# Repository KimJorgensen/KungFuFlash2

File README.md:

# Kung Fu Flash 2

The version in the repo is optimized for mass production, is 100% SMT

Cartridge for the Commodore 64 that packs a punch.

Kung Fu Flash 2 is the big brother of [Kung Fu Flash](https://github.com/KimJorgensen/KungFuFlash). It has a faster microcontroller with more memory and I/O pins, allowing for additional functionality.

**Currently, this project is considered experimental** and provides the same features as Kung Fu Flash, with these notable exceptions:

* CRT files are loaded into RAM, not flash, making large CRT files startup faster. However, changes to EasyFlash cartridges are lost if power is turned off, unless saved via the menu first
* The cartridge detects if the C64/C128 is reset. This allows the use of an additional reset button on the C64 or the built-in reset button on the C128
* REU emulation has been added

Kung Fu Flash 2 can emulate different cartridge types, load PRG files and use D64 disk images.
Just place your desired CRT, PRG or D64 files on a FAT formatted microSD card and use the built-in launcher to execute them.

## Hardware

There are three buttons on the cartridge; a reset button, a menu button for starting the launcher, and a special button that is used by the freezer cartridges.

The form factor is similar to Kung Fu Flash and it should be possible to use the same cartridge cases.
It could be the Stumpy Cartridge Case from TFW8b or the 3D printed cartridge case designed by bigby, [see here](https://www.thingiverse.com/thing:4153414).

The gerber files and BOM can be found [here](https://github.com/KimJorgensen/KungFuFlash2/releases/tag/v2.00).

## Supported Cartridges

The following cartridge types are currently supported:

* Generic cartridge (8k, 16k, Ultimax)
* Action Replay v4.x/v5/v6
* KCS Power Cartridge
* Final Cartridge III(+)
* Simons' BASIC
* Fun Play, Power Play
* Super Games
* Ocean type 1
* Epyx Fastload
* C64 Game System, System 3
* WarpSpeed
* Dinamic
* Zaxxon, Super Zaxxon
* Magic Desk, Domark, HES Australia
* Super Snapshot v5
* Comal-80
* Ross
* EasyFlash
* Prophet64
* Freeze Frame
* Freeze Machine
* MACH 5
* Pagefox
* RGCD, Hucky
* Drean
* C128 Generic cartridge (external function ROM)
* WarpSpeed 128

## Supported File Types

The following file types are currently supported:

* Cartridge (CRT)
* C64/C128 generic cartridge (ROM, BIN)
* Disk image (D64, D71, D81)
* Tape image (T64)
* Program (PRG, P00)
* Firmware update (UPD)
* Text document (TXT, NFO, 1ST)

## REU Emulation

Kung Fu Flash 2 can emulate a 1 Mb REU (RAM Expansion Unit) simultaneously with disk drive emulation.
The REU is enabled in the settings menu (F5) and active when:

* A program is executed using the default option (RETURN)
* A disk image or directory is mounted using "Mount" in the file options menu (SHIFT+RETURN)
* BASIC is started via F6 (C128) or F7 (C64) in the launcher

The REU will not be active when emulating cartridges (CRT files)

## USB Port

The USB port allows programs or disk images to be transferred from/to a PC using the EasyFlash 3 USB protocol.
The USB port is active when:

* The Kung Fu Flash 2 launcher is running
* A program is started using "Load" in the file options menu (SHIFT+RETURN)
* BASIC is started via F7 in the launcher **and** REU emulation is disabled in the settings menu (F5)

Kung Fu Flash 2 shows up as a standard serial port when connected to a PC not requiring any custom drivers to be installed.
This means, however, that the EasyFlash 3 program on the PC side must be modified to support Kung Fu Flash.

The repository of the original Kung Fu Flash contains a modified version of [EasyFlash 3 USB Utilities](https://github.com/KimJorgensen/KungFuFlash/tree/master/3rd_party/ef3utils)
and [EasyFlash 3 BBS](https://github.com/KimJorgensen/KungFuFlash/tree/master/3rd_party/ef3bbs) which will also work with the Kung Fu Flash 2.

## Firmware Update

Just place the KungFuFlash_v2.xx.upd file on the SD card and select the file in the launcher to initiate the firmware update.
The newest firmware can be found [here](https://github.com/KimJorgensen/KungFuFlash2/releases/).

For initial firmware installation, [see here](firmware/README.md).

## Limitations

Kung Fu Flash 2 is a so called Software Defined Cartridge where a fast microcontroller emulates cartridge hardware in software.
This makes it extremely flexible, allowing different cartridge types to be supported at a relative low cost.

However, it can be challenging to get the C64 bus timing correct in software and in some places the timing is very close to the limit.
Even though Kung Fu Flash 2 has been tested on different models of the Commodore 64, there is a chance that it doesn't work correctly on your specific model, or requires [phi2 offset adjustment](firmware/README.md#diagnostic).
Use it at your own risk!

Kung Fu Flash 2 will work with the PAL and NTSC version of the Commodore 64 or Commodore 128.

Disk drive emulation is using kernal vectors and will not work with fast loaders or software that uses direct hardware access which a lot of games does.
Currently REL files are not supported and only a subset of the Commodore DOS commands are supported.

## Thanks

Kung Fu Flash 2 was based on or uses other open source projects:

* [Kung Fu Flash](https://github.com/KimJorgensen/KungFuFlash)
* [EasyFlash 3](https://bitbucket.org/skoe/easyflash) by Thomas Giesel
* [Draco Browser](https://csdb.dk/release/?id=89910) by Sascha Bader
* [fatfs-stm32](https://github.com/colosimo/fatfs-stm32) by Aurelio Colosimo
* [FatFs](http://elm-chan.org/fsw/ff/00index_e.html) by ChaN
* [libusb_stm32](https://github.com/dmitrystu/libusb_stm32) by Dmitry Filimonchuk
* [OpenC64Cart](https://github.com/SukkoPera/OpenC64Cart) by Giorgioggì
* [Disk2easyflash](https://csdb.dk/release/?id=150323) by ALeX Kazik

and a few others. Please check the individual files for their license.

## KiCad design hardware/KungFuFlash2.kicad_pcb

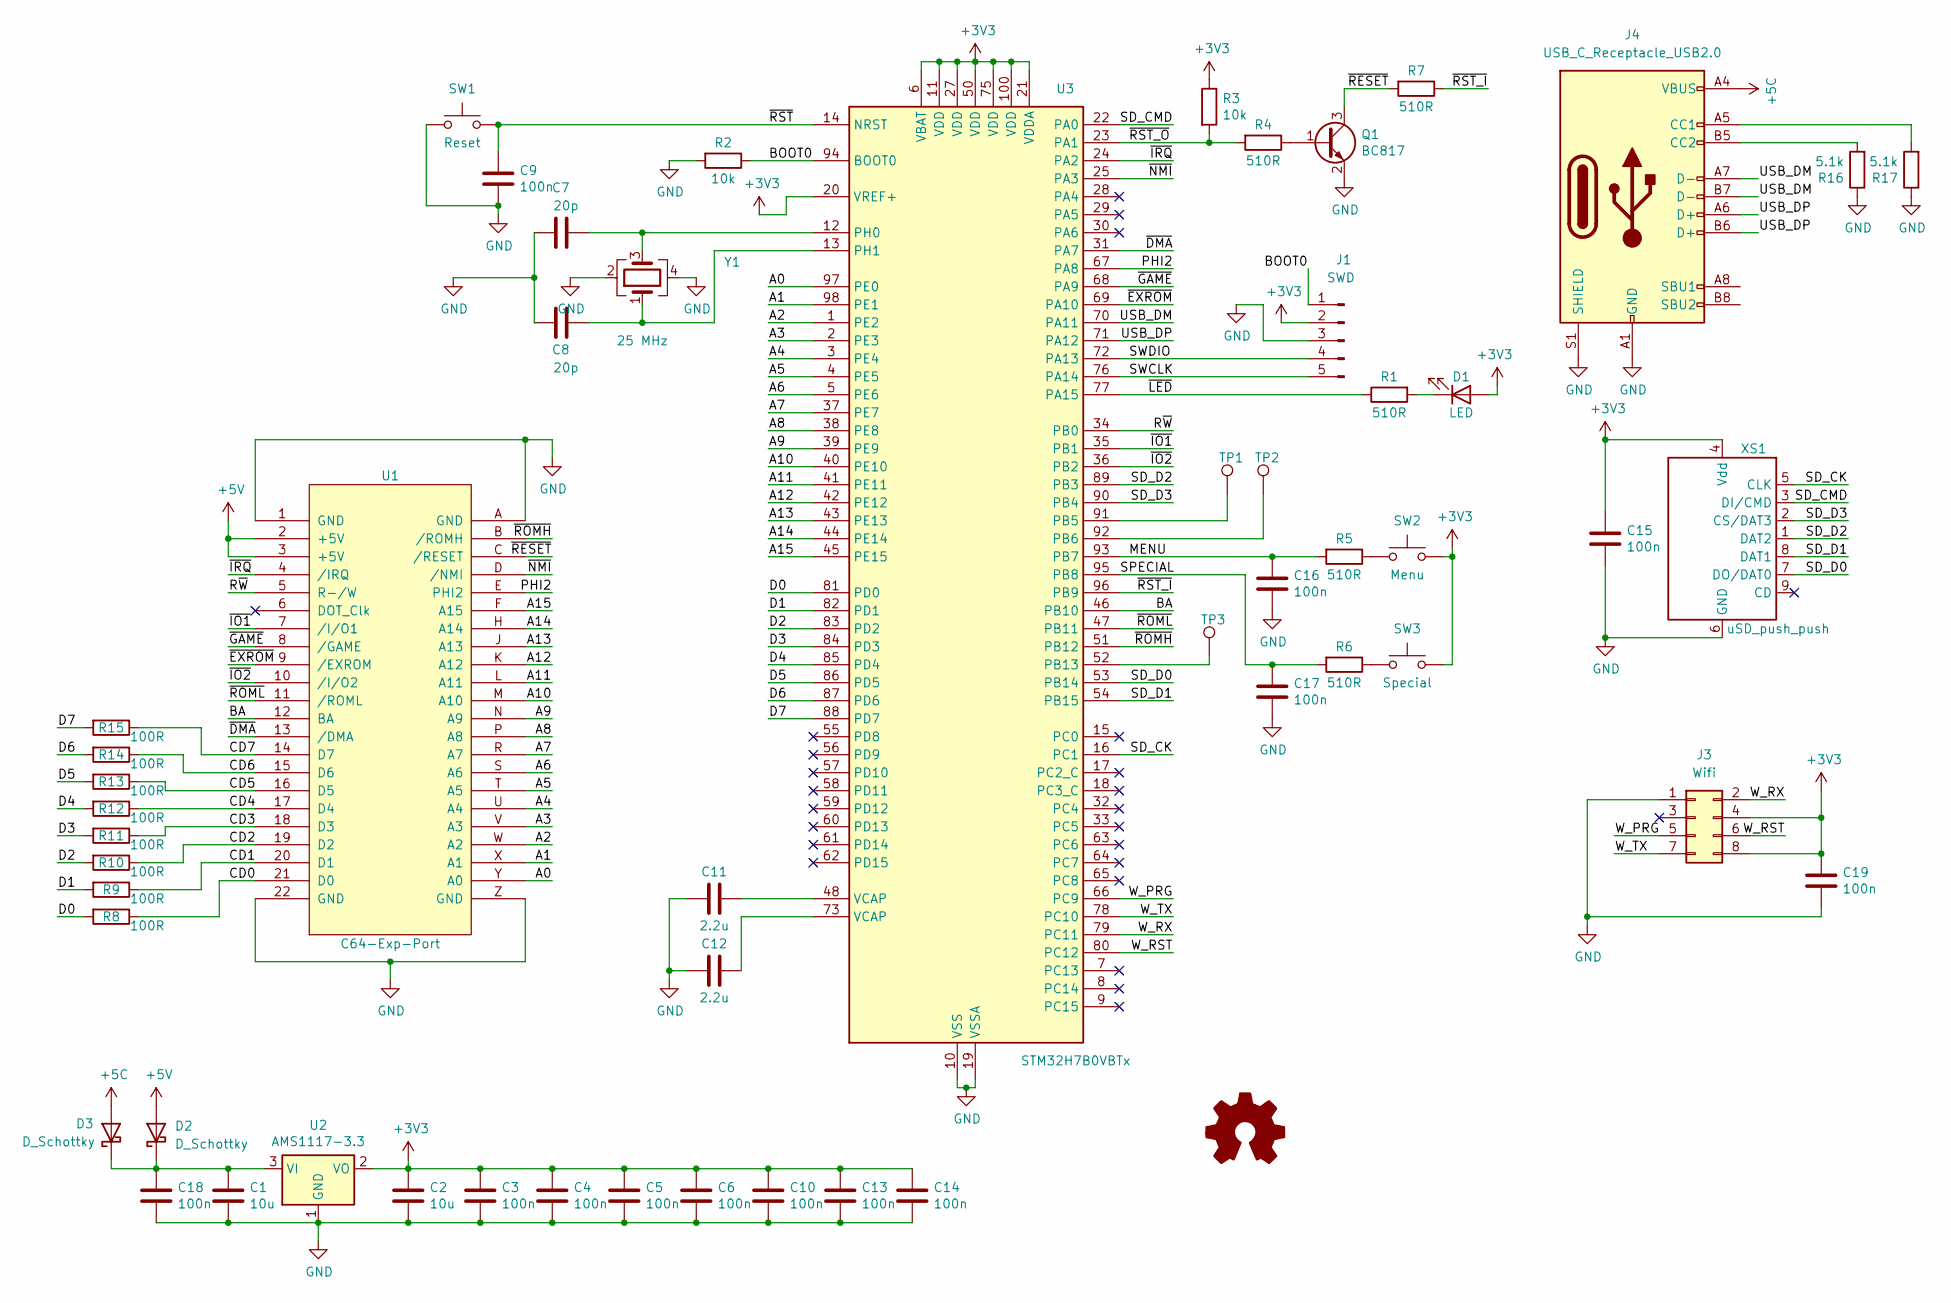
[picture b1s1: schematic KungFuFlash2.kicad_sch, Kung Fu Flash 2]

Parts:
C1, C2: 10u; C_0805_2012Metric_Pad1.18x1.45mm_HandSolder
C3, C4, C5, C6, C9, C10, C13, C14, C15, C16, C17, C18, C19: 100n; C_0603_1608Metric_Pad1.08x0.95mm_HandSolder
C7, C8: 20p; C_0603_1608Metric_Pad1.08x0.95mm_HandSolder
C11, C12: 2.2u; C_0805_2012Metric_Pad1.18x1.45mm_HandSolder
D1: LED; LED_0805_2012Metric_Pad1.15x1.40mm_HandSolder
D2, D3: D_Schottky; D_SMA_Handsoldering
J1: SWD; PinHeader_1x05_P2.54mm_Vertical
J3: Wifi; PinSocket_2x04_P2.54mm_Vertical
J4: USB_C_Receptacle_USB2.0; USB_C_Receptacle_XKB_U262-16XN-4BVC11
Q1: BC817; SOT-23
R1, R4, R5, R6, R7: 510R; R_0805_2012Metric_Pad1.20x1.40mm_HandSolder
R2, R3: 10k; R_0805_2012Metric_Pad1.20x1.40mm_HandSolder
R8, R9, R10, R11, R12, R13, R14, R15: 100R; R_0805_2012Metric_Pad1.20x1.40mm_HandSolder
R16, R17: 5.1k; R_0805_2012Metric_Pad1.20x1.40mm_HandSolder
SW1: Reset; SW_SPST_PTS645
SW2: Menu; SW_SPST_PTS645
SW3: Special; SW_SPST_PTS645
TP1, TP2, TP3: TestPoint_Pad_1.0x1.0mm
U1: C64-Exp-Port; C64-Cart
U2: AMS1117-3.3; SOT-223-3_TabPin2
U3: STM32H7B0VBTx; LQFP-100_14x14mm_P0.5mm
XS1: uSD_push_push; Conn_uSDcard
Y1: 25 MHz; Crystal_SMD_3225-4Pin_3.2x2.5mm

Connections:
+3V3: C2.1, C3.1, C4.1, C5.1, C6.1, C10.1, C13.1, C14.1, C15.1, C19.1, D1.2 (A), J1.2, J3.4, J3.8, R3.1, SW2.1, SW3.1, U2.2 (VO), U3.6 (VBAT), U3.11 (VDD), U3.20 (VREF+), U3.21 (VDDA), U3.27 (VDD), U3.50 (VDD), U3.75 (VDD), U3.100 (VDD), XS1.4 (Vdd)
+5C: D3.2 (A), J4.A4 (VBUS), J4.A9 (VBUS), J4.B4 (VBUS), J4.B9 (VBUS)
+5V: D2.2 (A), U1.2 (+5V), U1.3 (+5V)
/A0: U1.Y (A0), U3.97 (PE0)
/A1: U1.X (A1), U3.98 (PE1)
/A2: U1.W (A2), U3.1 (PE2)
/A3: U1.V (A3), U3.2 (PE3)
/A4: U1.U (A4), U3.3 (PE4)
/A5: U1.T (A5), U3.4 (PE5)
/A6: U1.S (A6), U3.5 (PE6)
/A7: U1.R (A7), U3.37 (PE7)
/A8: U1.P (A8), U3.38 (PE8)
/A9: U1.N (A9), U3.39 (PE9)
/A10: U1.M (A10), U3.40 (PE10)
/A11: U1.L (A11), U3.41 (PE11)
/A12: U1.K (A12), U3.42 (PE12)
/A13: U1.J (A13), U3.43 (PE13)
/A14: U1.H (A14), U3.44 (PE14)
/A15: U1.F (A15), U3.45 (PE15)
/BA: U1.12 (BA), U3.46 (PB10)
/BOOT0: J1.1, R2.1, U3.94 (BOOT0)
/CD0: R8.1, U1.21 (D0)
/CD1: R9.1, U1.20 (D1)
/CD2: R10.1, U1.19 (D2)
/CD3: R11.1, U1.18 (D3)
/CD4: R12.1, U1.17 (D4)
/CD5: R13.1, U1.16 (D5)
/CD6: R14.1, U1.15 (D6)
/CD7: R15.1, U1.14 (D7)
/D0: R8.2, U3.81 (PD0)
/D1: R9.2, U3.82 (PD1)
/D2: R10.2, U3.83 (PD2)
/D3: R11.2, U3.84 (PD3)
/D4: R12.2, U3.85 (PD4)
/D5: R13.2, U3.86 (PD5)
/D6: R14.2, U3.87 (PD6)
/D7: R15.2, U3.88 (PD7)
/MENU: C16.1, R5.2, U3.93 (PB7)
/PHI2: U1.E (PHI2), U3.67 (PA8)
/R~W: U1.5 (R-/W), U3.34 (PB0)
/SD_CK: U3.16 (PC1), XS1.5 (CLK)
/SD_CMD: U3.22 (PA0), XS1.3 (DI/CMD)
/SD_D0: U3.53 (PB14), XS1.7 (DO/DAT0)
/SD_D1: U3.54 (PB15), XS1.8 (DAT1)
/SD_D2: U3.89 (PB3), XS1.1 (DAT2)
/SD_D3: U3.90 (PB4), XS1.2 (CS/DAT3)
/SPECIAL: C17.1, R6.2, U3.95 (PB8)
/SWCLK: J1.5, U3.76 (PA14)
/SWDIO: J1.4, U3.72 (PA13)
/USB_DM: J4.A7 (D-), J4.B7 (D-), U3.70 (PA11)
/USB_DP: J4.A6 (D+), J4.B6 (D+), U3.71 (PA12)
/W_PRG: J3.5, U3.66 (PC9)
/W_RST: J3.6, U3.80 (PC12)
/W_RX: J3.2, U3.79 (PC11)
/W_TX: J3.7, U3.78 (PC10)
/~DMA: U1.13 (/DMA), U3.31 (PA7)
/~EXROM: U1.9 (/EXROM), U3.69 (PA10)
/~GAME: U1.8 (/GAME), U3.68 (PA9)
/~IO1: U1.7 (/I/O1), U3.35 (PB1)
/~IO2: U1.10 (/I/O2), U3.36 (PB2)
/~IRQ: U1.4 (/IRQ), U3.24 (PA2)
/~LED: R1.1, U3.77 (PA15)
/~NMI: U1.D (/NMI), U3.25 (PA3)
/~RESET: Q1.3 (C), R7.2, U1.C (/RESET)
/~ROMH: U1.B (/ROMH), U3.51 (PB12)
/~ROML: U1.11 (/ROML), U3.47 (PB11)
/~RST_I: R7.1, U3.96 (PB9)
/~RST_O: R3.2, R4.2, U3.23 (PA1)
/~RST: C9.1, SW1.2, U3.14 (NRST)
GND: C1.2, C2.2, C3.2, C4.2, C5.2, C6.2, C7.1, C8.1, C9.2, C10.2, C11.1, C12.2, C13.2, C14.2, C15.2, C16.2, C17.2, C18.2, C19.2, J1.3, J3.1, J4.A1 (GND), J4.A12 (GND), J4.B1 (GND), J4.B12 (GND), J4.S1 (SHIELD), Q1.2 (E), R2.2, R16.1, R17.1, SW1.1, U1.1 (GND), U1.22 (GND), U1.A (GND), U1.Z (GND), U2.1 (GND), U3.10 (VSS), U3.19 (VSSA), U3.26 (VSS), U3.49 (VSS), U3.74 (VSS), U3.99 (VSS), XS1.6 (GND), Y1.2, Y1.4
unnamed: C11.2, U3.48 (VCAP)
unnamed: C12.1, U3.73 (VCAP)
unnamed: D1.1 (K), R1.2
unnamed: C1.1, C18.1, D2.1 (K), D3.1 (K), U2.3 (VI)
unnamed: J4.A5 (CC1), R17.2
unnamed: J4.B5 (CC2), R16.2
unnamed: Q1.1 (B), R4.1
unnamed: R5.1, SW2.2
unnamed: R6.1, SW3.2
unnamed: TP1.1, U3.91 (PB5)
unnamed: TP2.1, U3.92 (PB6)
unnamed: TP3.1, U3.52 (PB13)
unnamed: C7.2, U3.12 (PH0), Y1.3
unnamed: C8.2, U3.13 (PH1), Y1.1

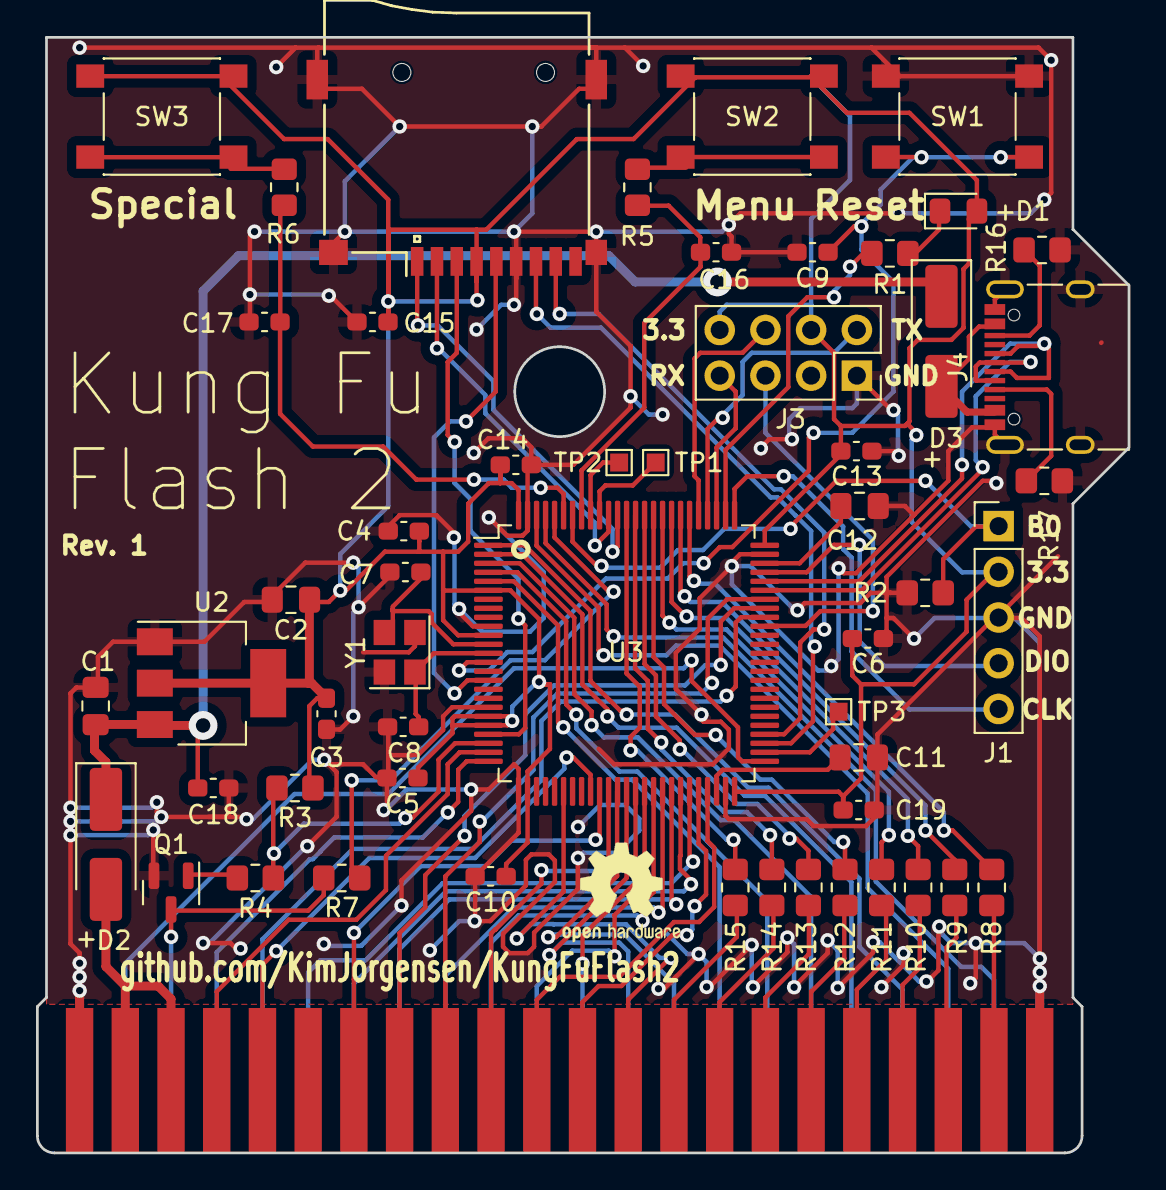
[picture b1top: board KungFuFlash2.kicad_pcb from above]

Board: 2 copper layers, 60.6 x 62.0 mm, 54 parts (0 on the bottom side), 84 nets.

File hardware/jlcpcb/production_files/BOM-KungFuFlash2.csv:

Comment,Designator,Footprint,LCSC
uSD_push_push,XS1,Conn_uSDcard,C111196
100n,"C10,C13,C14,C15,C16,C17,C18,C19,C3,C4,C5,C6,C9",C_0603_1608Metric_Pad1.08x0.95mm_HandSolder,C14663
10u,"C1,C2",C_0805_2012Metric_Pad1.18x1.45mm_HandSolder,C15850
20p,"C7,C8",C_0603_1608Metric_Pad1.08x0.95mm_HandSolder,C1648
USB_C_Receptacle_USB2.0,J4,USB_C_Receptacle_XKB_U262-16XN-4BVC11,C165948
100R,"R10,R11,R12,R13,R14,R15,R8,R9",R_0805_2012Metric_Pad1.20x1.40mm_HandSolder,C17408
10k,"R2,R3",R_0805_2012Metric_Pad1.20x1.40mm_HandSolder,C17414
510R,"R1,R4,R5,R6,R7",R_0805_2012Metric_Pad1.20x1.40mm_HandSolder,C17734
BC817,Q1,SOT-23,C2145
LED,D1,LED_0805_2012Metric_Pad1.15x1.40mm_HandSolder,C2297
5.1k,"R16,R17",R_0805_2012Metric_Pad1.20x1.40mm_HandSolder,C27834
2.2u,"C11,C12",C_0805_2012Metric_Pad1.18x1.45mm_HandSolder,C377773
AMS1117-3.3,U2,SOT-223-3_TabPin2,C6186
D_Schottky,"D2,D3",D_SMA_Handsoldering,C64998
STM32H7B0VBTx,U3,LQFP-100_14x14mm_P0.5mm,C730227
25 MHz,Y1,Crystal_SMD_3225-4Pin_3.2x2.5mm,C9006
Menu,SW2,SW_PUSH_6mm_H8mm,
C64-Exp-Port,U1,C64-Cart,
Special,SW3,SW_PUSH_6mm_H8mm,
Reset,SW1,SW_PUSH_6mm_H8mm,
~,TP2,TestPoint_Pad_1.0x1.0mm,
~,TP3,TestPoint_Pad_1.0x1.0mm,
~,TP1,TestPoint_Pad_1.0x1.0mm,
Wifi,J3,PinSocket_2x04_P2.54mm_Vertical,
SWD,J1,PinHeader_1x05_P2.54mm_Vertical,

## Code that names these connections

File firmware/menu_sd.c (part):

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                 memcmp("CBM", &crt_buf[0x4007], 3) == 0))
            {
                cfg_file.crt.type = CRT_C128_NORMAL_CARTRIDGE;
                cfg_file.crt.exrom = 1;
                cfg_file.crt.game = 1;

                if (!crt_is_supported(cfg_file.crt.type))
                {
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            else if (len && len <= 16*1024)
            {
                cfg_file.crt.type = CRT_NORMAL_CARTRIDGE;
                cfg_file.crt.exrom = 0;
                cfg_file.crt.game = 0;
                // Look for C64 CRT identifier "CBM80"
                if (memcmp("\xc3""\xc2""\xcd""80", &crt_buf[0x0004], 5) == 0)
                {
                    if (len <= 8*1024)
                    {
                        cfg_file.crt.game = 1;
                    }
                }
                else    // Assume Ultimax
                {
                    cfg_file.crt.exrom = 1;
                    rom_mirror(len);

                    // Validate reset vector
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    return sd_handle_change_dir(state, "..", true);
}

static const MENU sd_menu = {
    .state = &sd_state,
    .dir = (u8 (*)(void *))sd_handle_dir,
    .dir_up = (u8 (*)(void *, bool))sd_handle_dir_up,
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    .select = (u8 (*)(void *, u8, u8))sd_handle_select
};

static const MENU *sd_menu_init(void)
{
    chdir_last();
    sd_state.page_no = 0;
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
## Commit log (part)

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2024-06-30 Add MACH 5 support from KFF v1.51
2024-12-28 Update issue templates
2025-01-04 Fix race condition in menu startup from KFF v1.52
2025-01-04 Minor text update
2025-03-06 Added support for ROSS, REXUTIL, and WESTERMAN
2025-03-25 Add USB C and JLCPCB files
2025-03-29 Ross support from KFF v1.53
2025-08-01 Add build workflow
2025-08-01 Add basic SID file support
2025-08-02 Add SID to PRG conversion option
2025-08-04 Convert and play SID files via PRG
2025-08-07 Update PCB for USBC resistors 5.1k and production files
2025-08-11 ci: upload firmware artifacts
2025-08-11 ci: update artifact upload action
2025-10-23 Initial code changes for launcher
    Sorted directories
    User configurable color scheme
2025-10-23 Initial commit for firmware
    Sorted directories
    User configurable color scheme
2025-11-30 Fix autoload of PRG
2025-12-16 Add files via upload
    Updated to match official firmware
2025-12-16 Add files via upload
    Updated version number
2025-12-16 Add files via upload
    added pictures
2025-12-16 Update README with new features and images
    Added configurable color scheme and updated images.
2025-12-16 SMT buttons
2025-12-18 Project is moved to Codeberg

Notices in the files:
firmware/menu_sd.c:
Copyright (c) 2019-2025 Kim Jørgensen
